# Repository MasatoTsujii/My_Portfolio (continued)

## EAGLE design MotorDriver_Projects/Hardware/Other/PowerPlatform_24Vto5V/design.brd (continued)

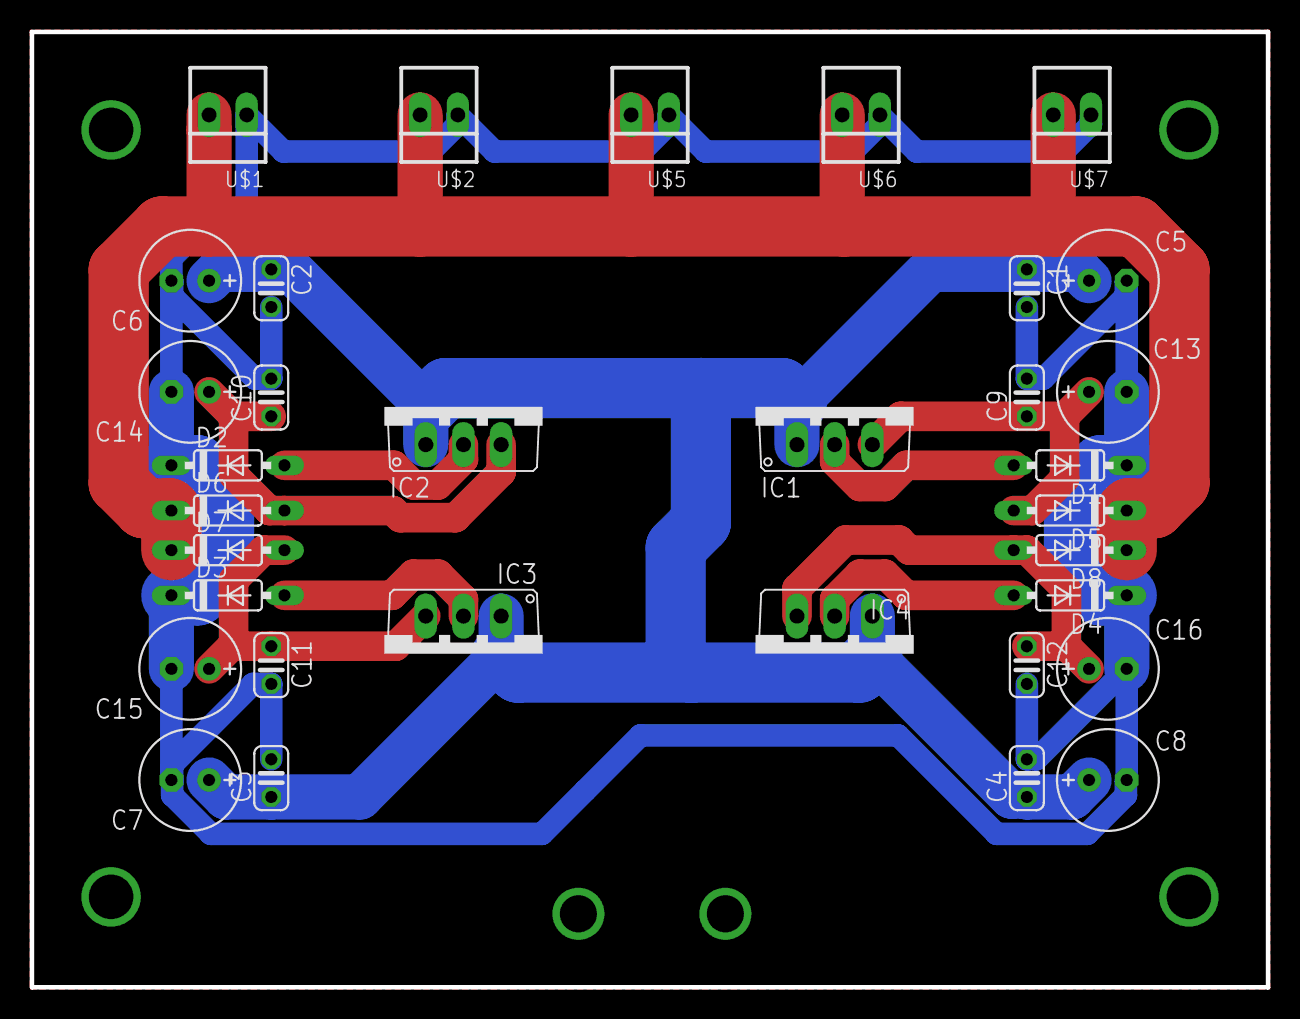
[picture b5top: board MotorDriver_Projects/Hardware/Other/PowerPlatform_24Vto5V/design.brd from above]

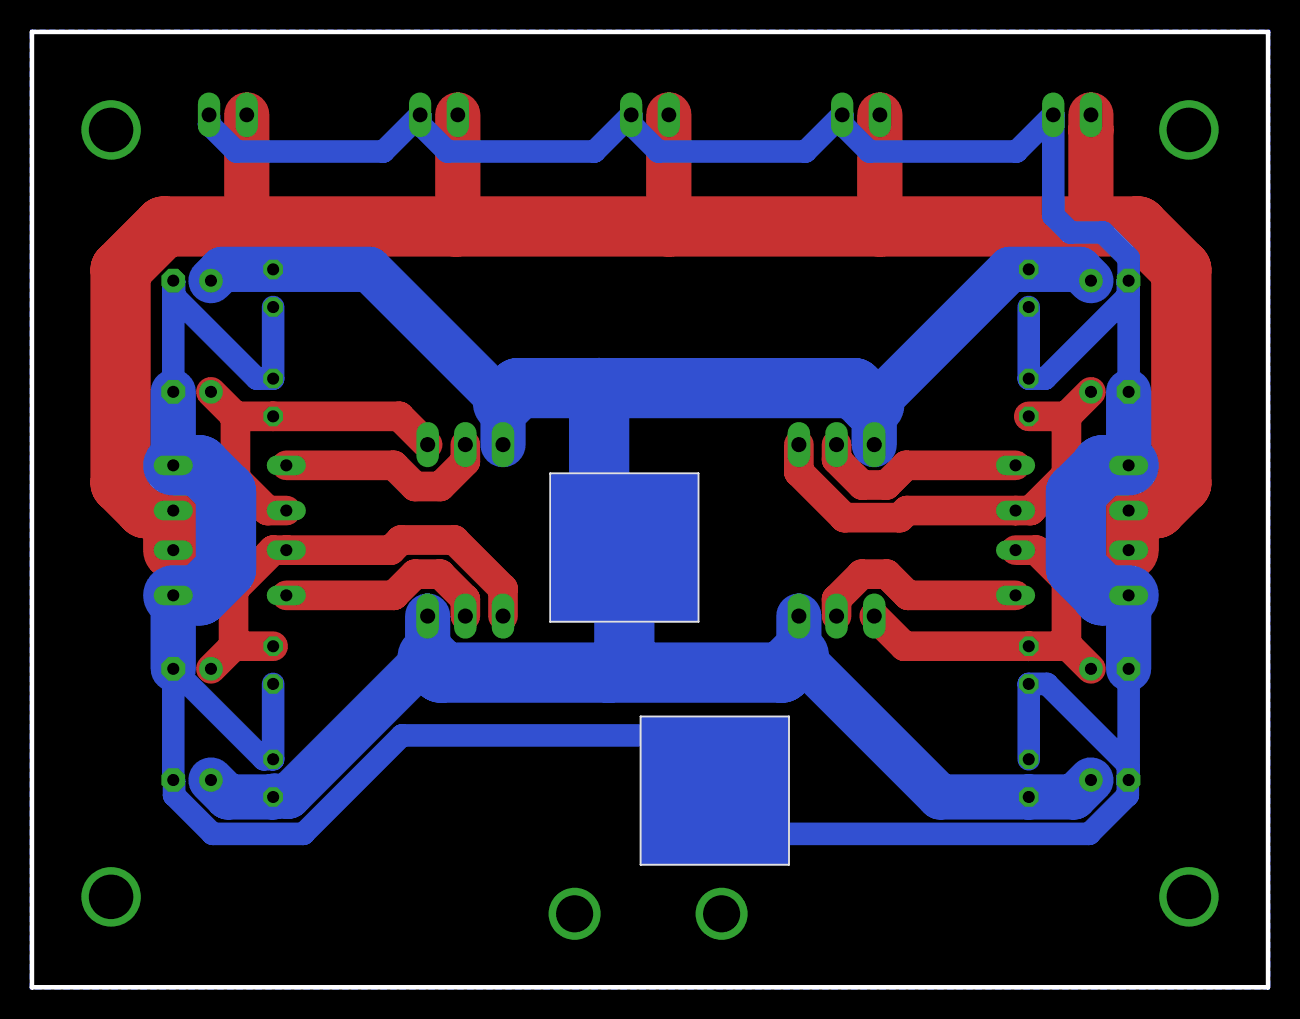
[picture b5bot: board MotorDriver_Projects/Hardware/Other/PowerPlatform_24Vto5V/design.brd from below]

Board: 2 copper layers, 83.3 x 64.4 mm, 35 parts (2 on the bottom side), 11 nets.

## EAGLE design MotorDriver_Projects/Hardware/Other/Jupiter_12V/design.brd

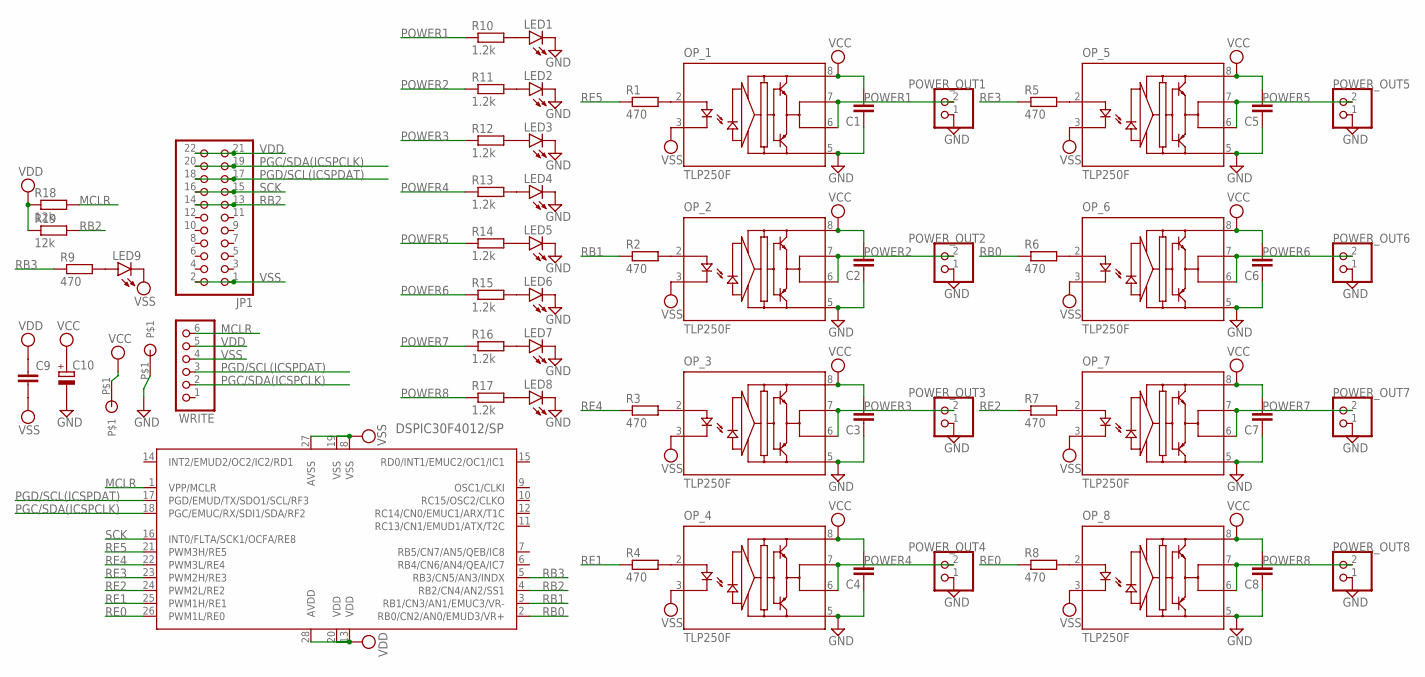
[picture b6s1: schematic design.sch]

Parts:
C1, C2, C3, C4, C5, C6, C7, C8, C9: C-EUC2012; C2012
C10: CPOL-EUE5-13; E5-13
IC1: DSPIC30F4012/SP; DIL28-3
JP1: PINHD-2X11/90; 2X11/90
LED1, LED2, LED3, LED4, LED5, LED6, LED7, LED8, LED9: LEDCHIPLED_0603; CHIPLED_0603
OP_1, OP_2, OP_3, OP_4, OP_5, OP_6, OP_7, OP_8: TLP250F; DIL08
POWER_OUT1, POWER_OUT2, POWER_OUT3, POWER_OUT4, POWER_OUT5, POWER_OUT6, POWER_OUT7, POWER_OUT8: PINHD-1X2/90; 1X02/90
R1, R2, R3, R4, R5, R6, R7, R8, R9: 470; M0805
R10, R11, R12, R13, R14, R15, R16, R17: 1.2k; M0805
R18, R19: 12k; M0805
U$1, U$8: MARU
WRITE: PINHD-1X6/90; 1X06/90

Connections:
GND: C1.2, C2.2, C3.2, C4.2, C5.2, C6.2, C7.2, C8.2, C10.-, LED1.C, LED2.C, LED3.C, LED4.C, LED5.C, LED6.C, LED7.C, LED8.C, OP_1.5 (GND), OP_2.5 (GND), OP_3.5 (GND), OP_4.5 (GND), OP_5.5 (GND), OP_6.5 (GND), OP_7.5 (GND), OP_8.5 (GND), POWER_OUT1.1, POWER_OUT2.1, POWER_OUT3.1, POWER_OUT4.1, POWER_OUT5.1, POWER_OUT6.1, POWER_OUT7.1, POWER_OUT8.1, U$1.P$1
MCLR: IC1.1 (VPP/MCLR), R18.2, WRITE.6
unnamed: OP_1.2 (A), R1.2
unnamed: OP_2.2 (A), R2.2
unnamed: OP_3.2 (A), R3.2
unnamed: OP_4.2 (A), R4.2
unnamed: OP_5.2 (A), R5.2
unnamed: OP_6.2 (A), R6.2
unnamed: OP_7.2 (A), R7.2
unnamed: OP_8.2 (A), R8.2
unnamed: LED9.A, R9.2
unnamed: LED1.A, R10.2
unnamed: LED2.A, R11.2
unnamed: LED3.A, R12.2
unnamed: LED4.A, R13.2
unnamed: LED5.A, R14.2
unnamed: LED6.A, R15.2
unnamed: LED8.A, R17.2
unnamed: LED7.A, R16.2
PGC/SDA(ICSPCLK): IC1.18 (PGC/EMUC/RX/SDI1/SDA/RF2), JP1.19, JP1.20, WRITE.2
PGD/SCL(ICSPDAT): IC1.17 (PGD/EMUD/TX/SDO1/SCL/RF3), JP1.17, JP1.18, WRITE.3
POWER1: OP_1.6 (VO), OP_1.7 (VO'), POWER_OUT1.2, R10.1
POWER2: OP_2.6 (VO), OP_2.7 (VO'), POWER_OUT2.2, R11.1
POWER3: OP_3.6 (VO), OP_3.7 (VO'), POWER_OUT3.2, R12.1
POWER4: OP_4.6 (VO), OP_4.7 (VO'), POWER_OUT4.2, R13.1
POWER5: OP_5.6 (VO), OP_5.7 (VO'), POWER_OUT5.2, R14.1
POWER6: OP_6.6 (VO), OP_6.7 (VO'), POWER_OUT6.2, R15.1
POWER7: OP_7.6 (VO), OP_7.7 (VO'), POWER_OUT7.2, R16.1
POWER8: OP_8.6 (VO), OP_8.7 (VO'), POWER_OUT8.2, R17.1
RB0: IC1.2 (RB0/CN2/AN0/EMUD3/VR+), R6.1
RB1: IC1.3 (RB1/CN3/AN1/EMUC3/VR-), R2.1
RB2: IC1.4 (RB2/CN4/AN2/SS1), JP1.13, JP1.14, R19.2
RB3: IC1.5 (RB3/CN5/AN3/INDX), R9.1
RE0: IC1.26 (PWM1L/RE0), R8.1
RE1: IC1.25 (PWM1H/RE1), R4.1
RE2: IC1.24 (PWM2L/RE2), R7.1
RE3: IC1.23 (PWM2H/RE3), R5.1
RE4: IC1.22 (PWM3L/RE4), R3.1
RE5: IC1.21 (PWM3H/RE5), R1.1
SCK: IC1.16 (INT0/FLTA/SCK1/OCFA/RE8), JP1.15, JP1.16
VCC: C1.1, C2.1, C3.1, C4.1, C5.1, C6.1, C7.1, C8.1, C10.+, OP_1.8 (VCC), OP_2.8 (VCC), OP_3.8 (VCC), OP_4.8 (VCC), OP_5.8 (VCC), OP_6.8 (VCC), OP_7.8 (VCC), OP_8.8 (VCC), U$8.P$1
VDD: C9.1, IC1.13 (VDD), IC1.20 (VDD), IC1.28 (AVDD), JP1.21, JP1.22, R18.1, R19.1, WRITE.5
VSS: C9.2, IC1.8 (VSS), IC1.19 (VSS), IC1.27 (AVSS), JP1.1, JP1.2, LED9.C, OP_1.3 (K), OP_2.3 (K), OP_3.3 (K), OP_4.3 (K), OP_5.3 (K), OP_6.3 (K), OP_7.3 (K), OP_8.3 (K), WRITE.4

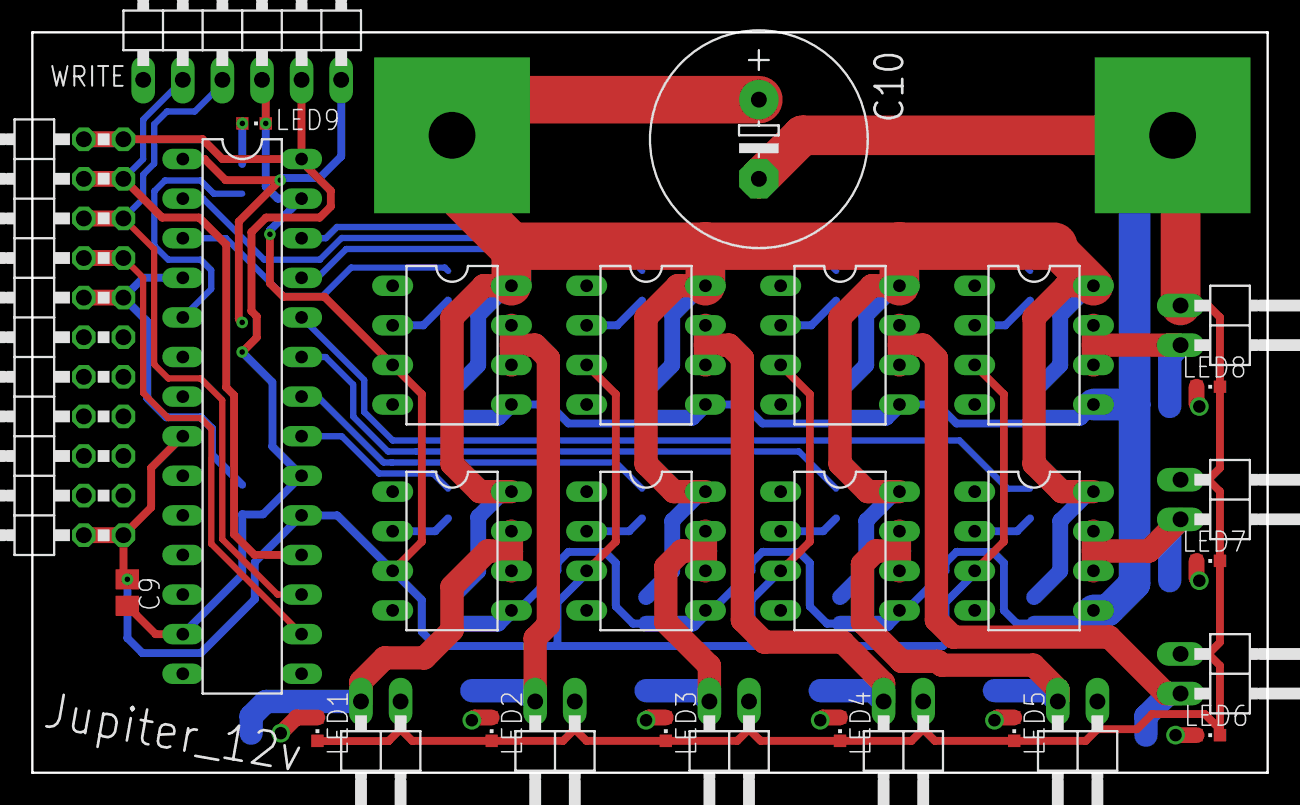
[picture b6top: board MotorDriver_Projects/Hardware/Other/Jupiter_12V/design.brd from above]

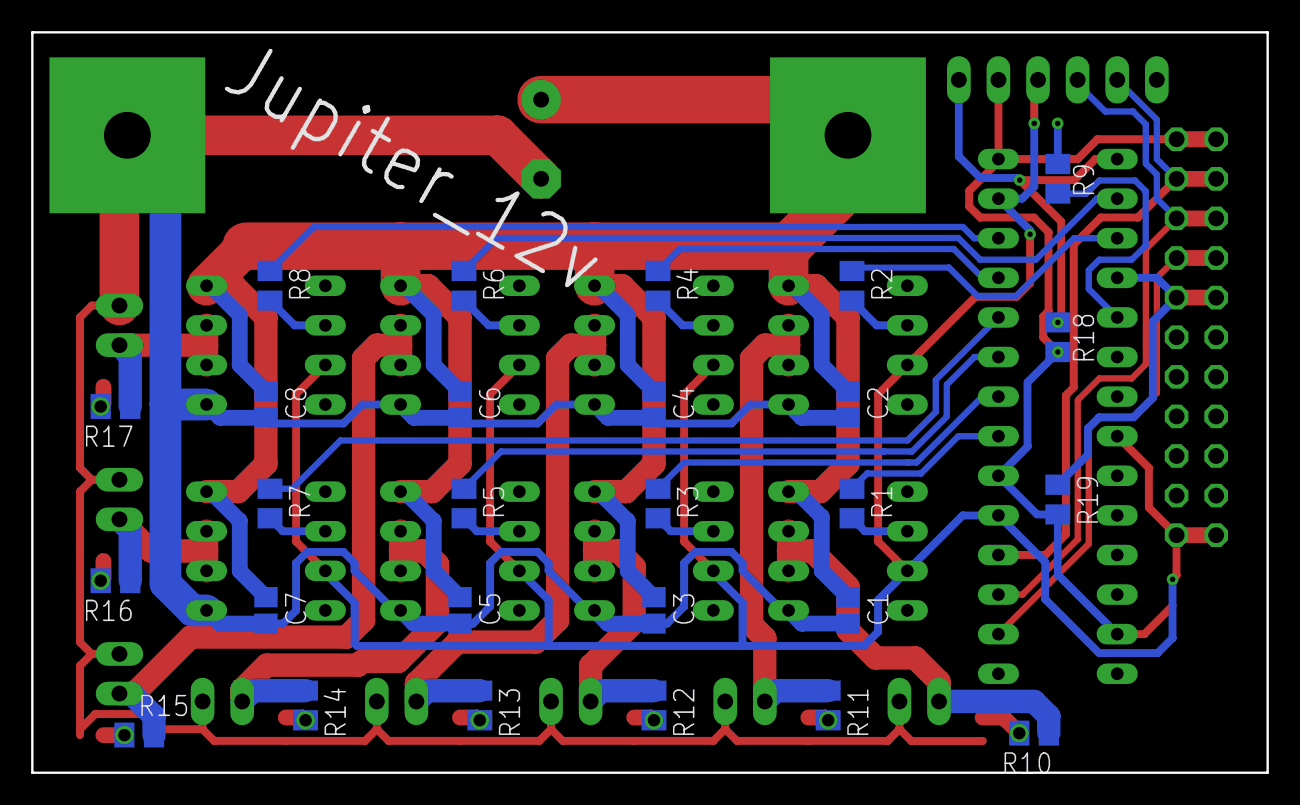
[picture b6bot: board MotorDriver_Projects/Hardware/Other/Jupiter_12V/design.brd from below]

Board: 2 copper layers, 79.2 x 47.5 mm, 59 parts (27 on the bottom side), 43 nets.

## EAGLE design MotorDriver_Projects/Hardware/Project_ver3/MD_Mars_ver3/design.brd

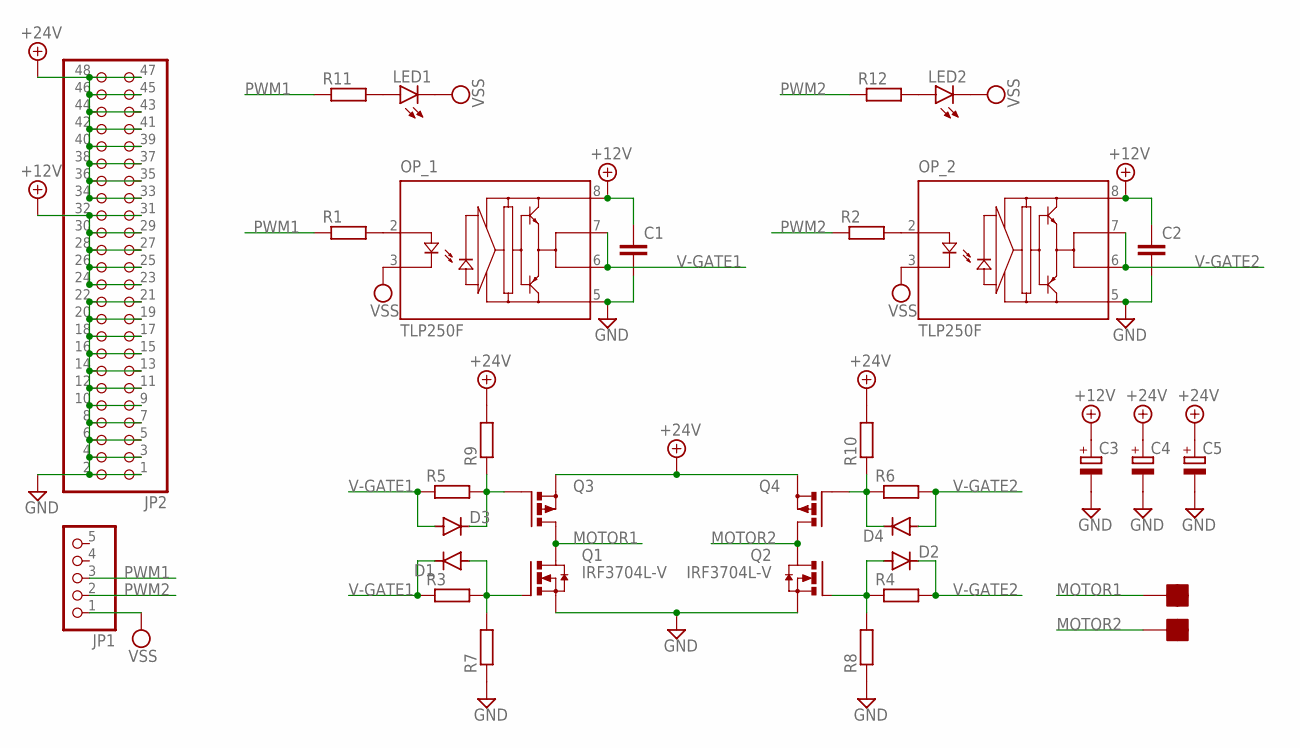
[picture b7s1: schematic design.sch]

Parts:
C1, C2: C-EUC2012; C2012
C3, C4, C5: CPOL-EUE5-13; E5-13
D1, D2, D3, D4: DIODE-SOD110-W; SOD110-W
JP1: PINHD-1X5/90; 1X05/90
JP2: PINHD-2X24/90; 2X24/90
LED1, LED2: LED5MM
OP_1, OP_2: TLP250F; DIL08
Q1, Q2: IRF3704L-V; TO262-V
Q3, Q4: PMOSFET_PTO220BV; TO220BV
R1, R2, R3, R4, R5, R6, R7, R8, R9, R10, R11, R12: R-EU_M0805; M0805
U$1, U$2: PLAT10.0X10.0; PLAT

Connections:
+12V: C1.1, C2.1, C3.+, JP2.23, JP2.24, JP2.25, JP2.26, JP2.27, JP2.28, JP2.29, JP2.30, JP2.31, JP2.32, OP_1.8 (VCC), OP_2.8 (VCC)
+24V: C4.+, C5.+, JP2.33, JP2.34, JP2.35, JP2.36, JP2.37, JP2.38, JP2.39, JP2.40, JP2.41, JP2.42, JP2.43, JP2.44, JP2.45, JP2.46, JP2.47, JP2.48, Q3.S, Q4.S, R9.2, R10.2
GND: C1.2, C2.2, C3.-, C4.-, C5.-, JP2.1, JP2.2, JP2.3, JP2.4, JP2.5, JP2.6, JP2.7, JP2.8, JP2.9, JP2.10, JP2.11, JP2.12, JP2.13, JP2.14, JP2.15, JP2.16, JP2.17, JP2.18, JP2.19, JP2.20, JP2.21, JP2.22, OP_1.5 (GND), OP_2.5 (GND), Q1.3 (S), Q2.3 (S), R7.1, R8.1
MOTOR1: Q1.2 (D), Q3.D, U$2.P$1
MOTOR2: Q2.2 (D), Q4.D, U$1.P$1
unnamed: D1.A, Q1.1 (G), R3.2, R7.2
unnamed: D3.C, Q3.G, R5.2, R9.1
unnamed: OP_1.2 (A), R1.2
unnamed: OP_2.2 (A), R2.2
unnamed: D4.C, Q4.G, R6.1, R10.1
unnamed: D2.A, Q2.1 (G), R4.1, R8.2
unnamed: LED1.A, R11.2
unnamed: LED2.A, R12.2
PWM1: JP1.3, R1.1, R11.1
PWM2: JP1.2, R2.1, R12.1
V-GATE1: D1.C, D3.A, OP_1.6 (VO), OP_1.7 (VO'), R3.1, R5.1
V-GATE2: D2.C, D4.A, OP_2.6 (VO), OP_2.7 (VO'), R4.2, R6.2
VSS: JP1.1, LED1.K (C), LED2.K (C), OP_1.3 (K), OP_2.3 (K)

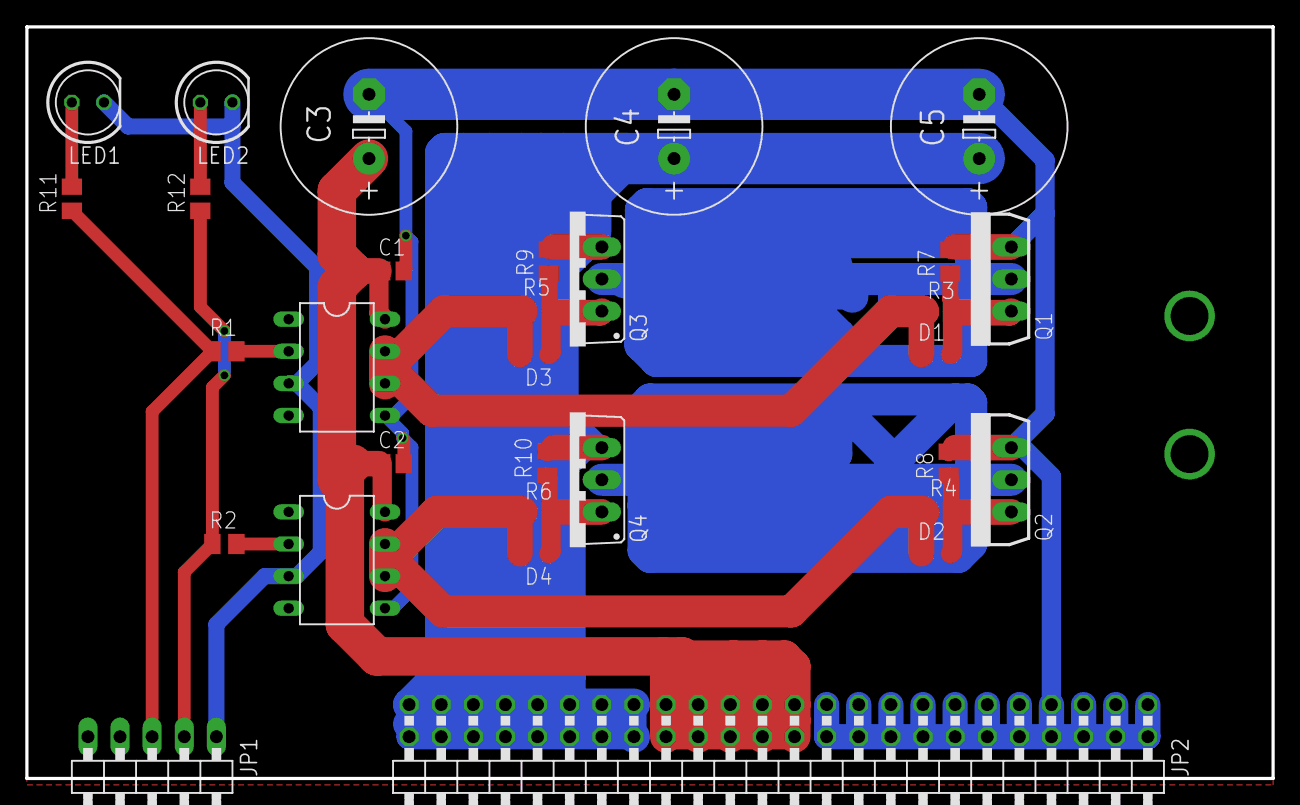
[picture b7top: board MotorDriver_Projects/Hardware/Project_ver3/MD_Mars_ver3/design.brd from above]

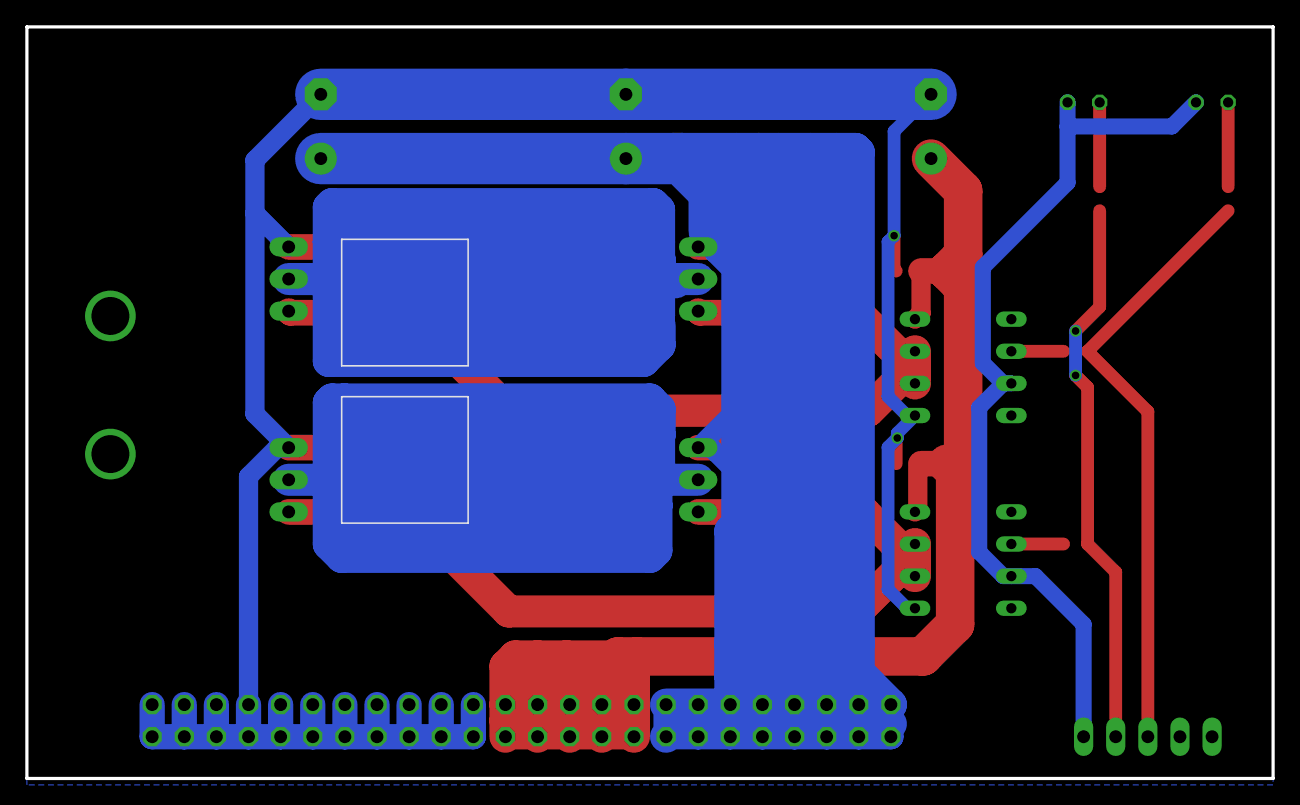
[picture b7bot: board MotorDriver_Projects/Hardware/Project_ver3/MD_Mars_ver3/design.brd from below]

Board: 2 copper layers, 98.6 x 59.4 mm, 33 parts (2 on the bottom side), 18 nets.

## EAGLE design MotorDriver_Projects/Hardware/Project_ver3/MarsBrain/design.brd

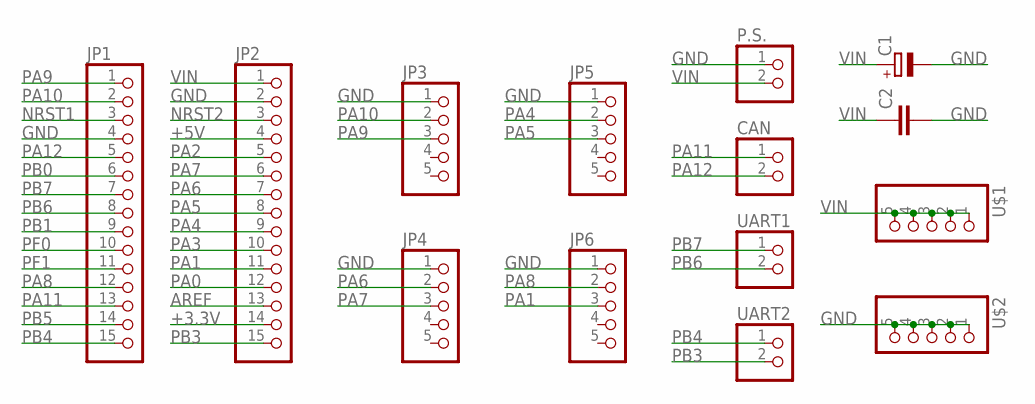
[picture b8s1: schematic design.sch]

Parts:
C1: CPOL-EUE2.5-7; E2,5-7
C2: C-EU025-024X044; C025-024X044
CAN: ABOUTERS_2PIN; 22-23-2021
JP1, JP2: PINHD-1X15; 1X15
JP3, JP4, JP5, JP6: PINHD-1X5/90; 1X05/90
P.S.: ABOUTERS_2PIN; 22-23-2021
U$1, U$2: ABOUTERS_5PIN; 22-23-2051
UART1, UART2: ABOUTERS_2PIN; 22-23-2021

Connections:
+3.3V: JP2.14
+5V: JP2.4
AREF: JP2.13
GND: C1.-, C2.2, JP1.4, JP2.2, JP3.1, JP4.1, JP5.1, JP6.1, P.S..1, U$2.1, U$2.2, U$2.3, U$2.4, U$2.5
NRST1: JP1.3
NRST2: JP2.3
PA0: JP2.12
PA1: JP2.11, JP6.3
PA2: JP2.5
PA3: JP2.10
PA4: JP2.9, JP5.2
PA5: JP2.8, JP5.3
PA6: JP2.7, JP4.2
PA7: JP2.6, JP4.3
PA8: JP1.12, JP6.2
PA9: JP1.1, JP3.3
PA10: JP1.2, JP3.2
PA11: CAN.1, JP1.13
PA12: CAN.2, JP1.5
PB0: JP1.6
PB1: JP1.9
PB3: JP2.15, UART2.2
PB4: JP1.15, UART2.1
PB5: JP1.14
PB6: JP1.8, UART1.2
PB7: JP1.7, UART1.1
PF0: JP1.10
PF1: JP1.11
VIN: C1.+, C2.1, JP2.1, P.S..2, U$1.1, U$1.2, U$1.3, U$1.4, U$1.5

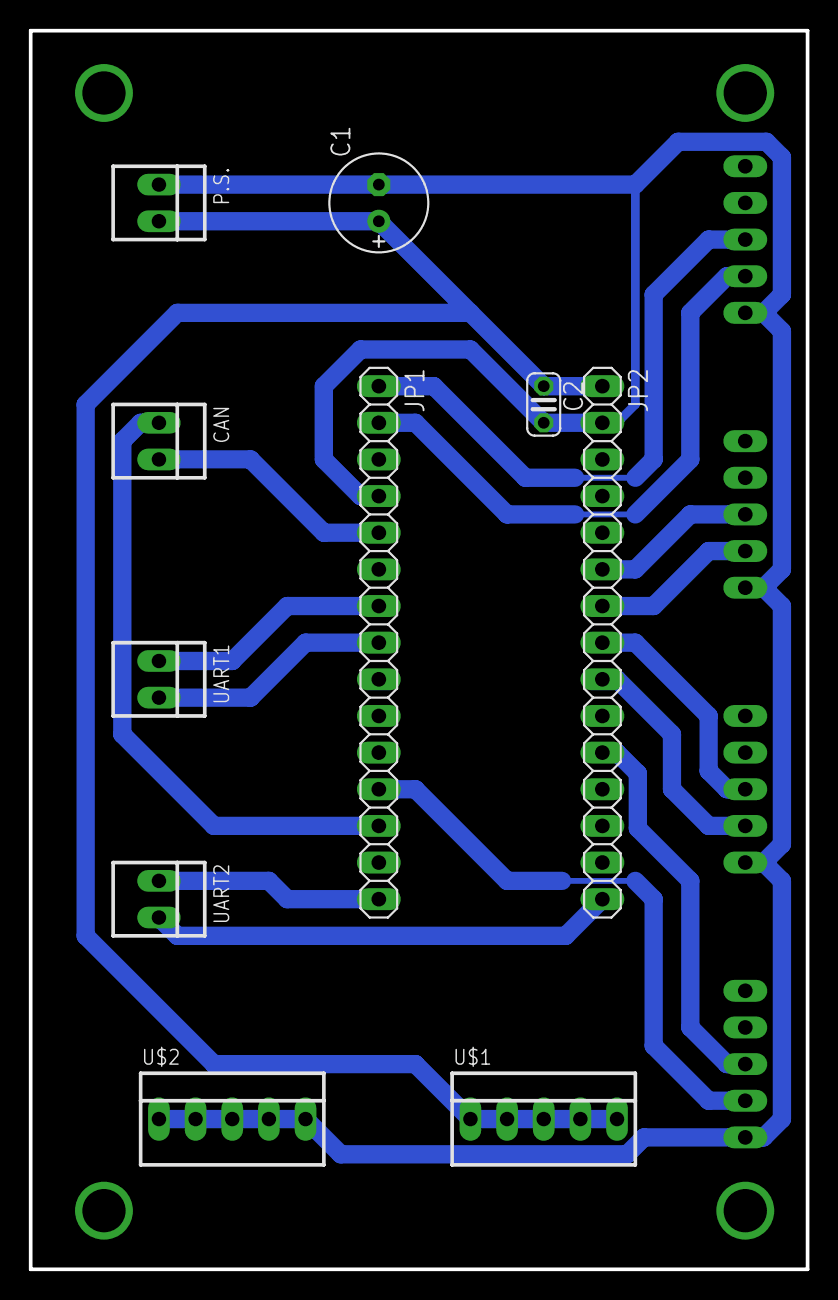
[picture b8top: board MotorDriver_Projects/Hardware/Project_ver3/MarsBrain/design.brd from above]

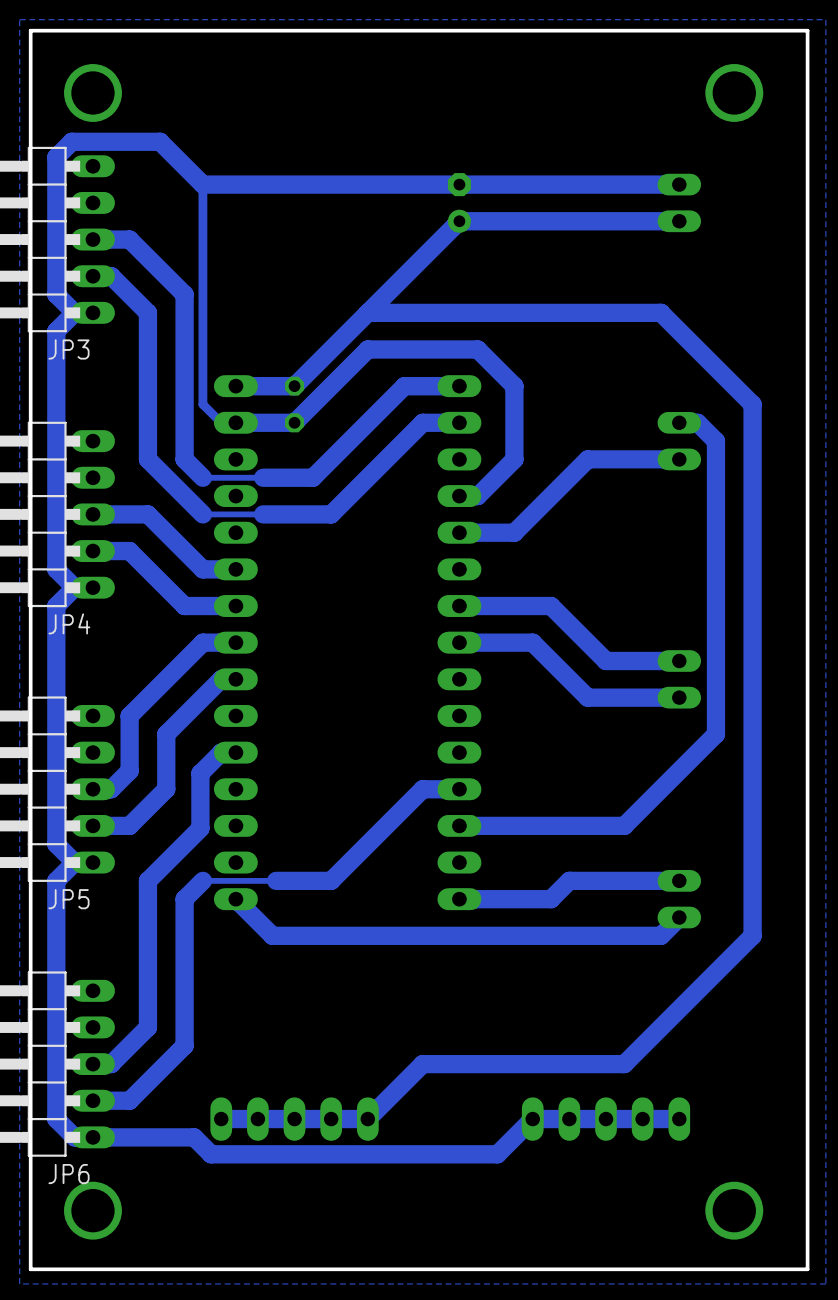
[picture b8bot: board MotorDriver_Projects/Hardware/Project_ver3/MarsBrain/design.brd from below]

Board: 2 copper layers, 53.8 x 85.9 mm, 14 parts (4 on the bottom side), 16 nets.

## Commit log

2026-01-30 Dynamixel制御基板の追加
    Season2020で使用したDynamixelを制御する自作基盤の回路図、基板データの元データとpdfファイルを追加。
    DynamixelはTTLという双方向のシリアル通信を行っていたため、ICを使い変換する必要があった
2026-01-30 ダイレクトティーチングを操作する基盤を追加
    Season2020で行ったダイレクトティーチング用の自作基盤の回路図、基板データの元データとpdfファイルを追加。
    Dynamixelを用い動作の実現可能性を知るために、ダイレクトティーチングを用いた。
2026-01-30 Create NucleoMB_Season2020
2026-01-30 Nucleo F446REのマザーボードを追加
    Season2020で使用したNucleo Board STM32 F446REのマザーボード。
2026-01-30 ミドルロボコン2020で使用した基板を追加
    モタドラが足りなくて作った基盤と新しく使い始めたマイコンボード用のマザーボードの回路図、基板データの元データとPDF。
2026-01-30 Season2019本番機のプログラムを追加
    洗濯物干し競技の本番機で使用していたプログラム。
    名前は適当に決めた
2026-01-30 Season2019試作機のプログラムを追加
    選択物干し競技の試作プログラム
2026-01-30 遠隔非常停止基板を追加
    ミドルロボコン2020で使用した遠隔非常停止。
    通信は確かSBDBTを使用したBluetoothのはず。
2026-01-30 Season2022のコントローラの写真を追加
    実際に制作したコントローラの画像。
    内部の写真はなかったため、外見のみ。
2026-01-30 Season2022のコントローラの画僧を追加
    紙飛行機を飛ばす競技で実際に使用したコントローラ。
    内部の写真はなかったので、外部のみ。
2026-01-30 Season2022のコントローラ関係の基板を追加
    Season2022で作成したコントローラ用のマザボ、通信機器（IM920）とジョイスティックの変換基板の回路図、基板データを追加。
    元データとPDFと3Dの画像データ。
2026-01-30 表面実装基板データの追加
    基板を表面実装化した基板の回路図、基板の元データとPDFファイル。
    主にモタドラを行ったが、電磁弁用や電源供給用の基板もある。
2026-01-30 表面実装基板データの追加
    基板を表面実装化した基板の回路図、基板の元データとPDFファイル。
    モタドラの在籍時の最終的なバージョンまで。このデータはKiCadで作成。
2026-01-30 Season2022のコントローラ関連のプログラム
    紙飛行機で急遽制作したコントローラのプログラム。
    通信機器の設定やディスプレイの表示など実験をしたプログラムもある。
2026-01-30 Marsの動作確認用プログラムの追加
    MD_Mars_ver4.00_prototypeの動作確認用プログラム。
2026-01-30 Season2020で使用したプログラムを追加
    ライブラリが豊富なArduinoでDynamixelの動作を確認した。
    その後ダイレクトティーチングのプログラムや本番の動作を制作した。
2026-01-31 ロボット画像の追加
2026-01-31 ディレクトリの場所を変更
2026-01-31 ディレクトリの変更
2026-01-31 ロボット、コントローラ画像の追加
2026-02-03 写真の追加
    当時作っていた電文表
